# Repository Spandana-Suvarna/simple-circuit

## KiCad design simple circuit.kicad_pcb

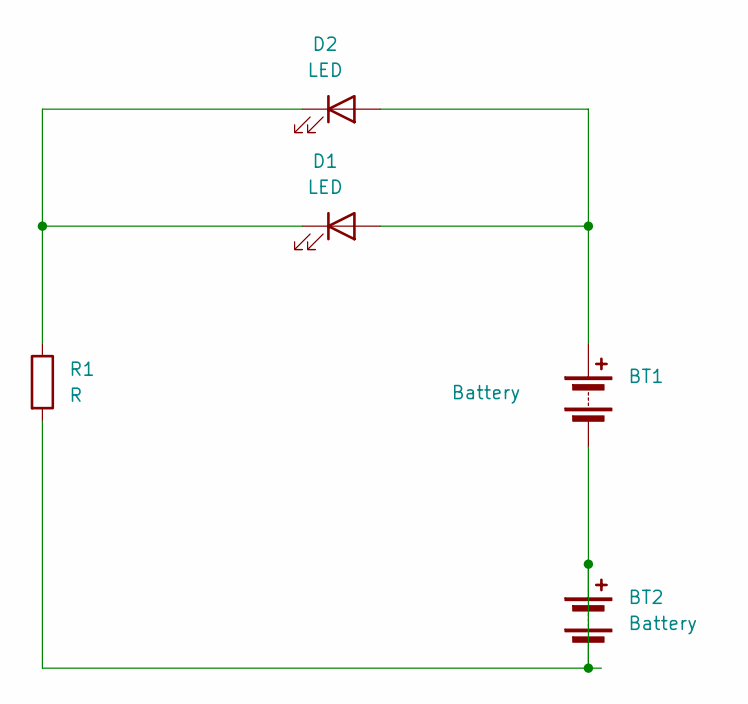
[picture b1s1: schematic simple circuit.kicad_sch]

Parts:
BT1, BT2: Battery; BatteryHolder_Keystone_500
D1, D2: LED; LED_D3.0mm
R1: R; R_Axial_Power_L38.0mm_W9.0mm_P40.64mm

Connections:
unnamed: BT1.1 (+), D1.2 (A), D2.2 (A)
unnamed: BT1.2 (-), BT2.1 (+), BT2.2 (-), R1.2
unnamed: D1.1 (K), D2.1 (K), R1.1

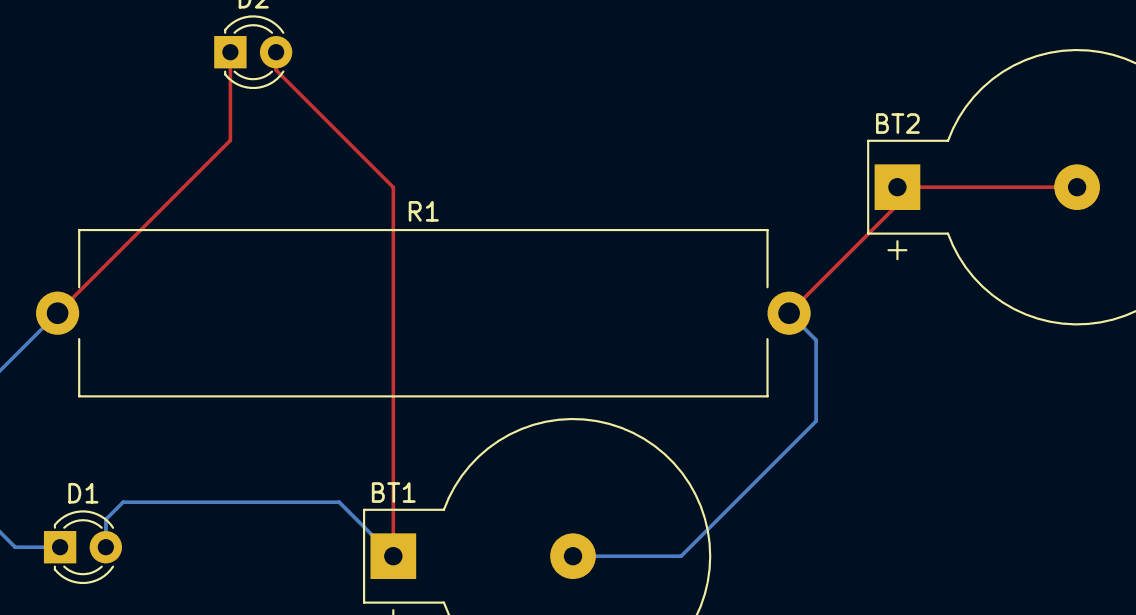
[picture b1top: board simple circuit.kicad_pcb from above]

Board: 2 copper layers, 5 parts (0 on the bottom side), 3 nets.

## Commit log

2025-04-22 this initial circuite
2025-04-22 2 battery and 2 led circuite
2025-04-22 Create read.txt
    hellooooooo
